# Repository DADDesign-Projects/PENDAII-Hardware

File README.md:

# PENDAII: Platform for Effects oN DAisy

Welcome to the **PENDAII** project! This repository contains the schematics and PCB layouts created with **KiCad 9.0** for a digital audio effects platform based on the **Daisy-Seed** board from **ElectroSmith**.

## Author

**DAD Design**

## Overview / Features

**PENDAII** is the second version of the PENDA platform. It introduces stereo processing and improved management of signal paths and power supplies.

**What’s New in PENDAII**:

- **Stereo processing**: a second audio channel has been added for a wider and more immersive sound experience.
- **Digital input volume control**: the input gain is now precisely adjustable via a digital potentiometer.
- **Digital Dry/Wet mix control**: the ratio between the processed (wet) and original (dry) signal is digitally managed.
- **100% analog Dry path**: although controlled digitally, the dry signal remains fully analog to preserve audio quality.

**General Features**:

- **Mono or Stereo Audio Input/Output**: flexible integration into various audio setups.
- **Two momentary footswitches**: for hands-free activation of effects.
- **2-inch SPI display**: clean and compact user interface (compatible with most ST7789 displays).
- **MIDI input**: allows control via external MIDI devices.
- **User controls**:
  - **4 encoders with push-button**: for parameter navigation and adjustment.
  - **3 analog potentiometers**: for direct control of parameters such as input level or Dry/Wet mix.

## Content

- The **Fab** directory contains all necessary files for fabrication.
- The **PENDAII-Hardware** directory contains the source files for the KiCad 9.0 project.

## Software

**PENDAII-Software** is a collection of audio effects built on an advanced software architecture, specifically designed for the PENDAII hardware platform.

[GitHub Repository](https://github.com/DADDesign-Projects/PENDAII-Software)

## Contributing

Contributions are welcome! If you'd like to suggest an improvement or fix an issue, feel free to open an *issue* or a *pull request*.

## License

This project is licensed under the **MIT License**.

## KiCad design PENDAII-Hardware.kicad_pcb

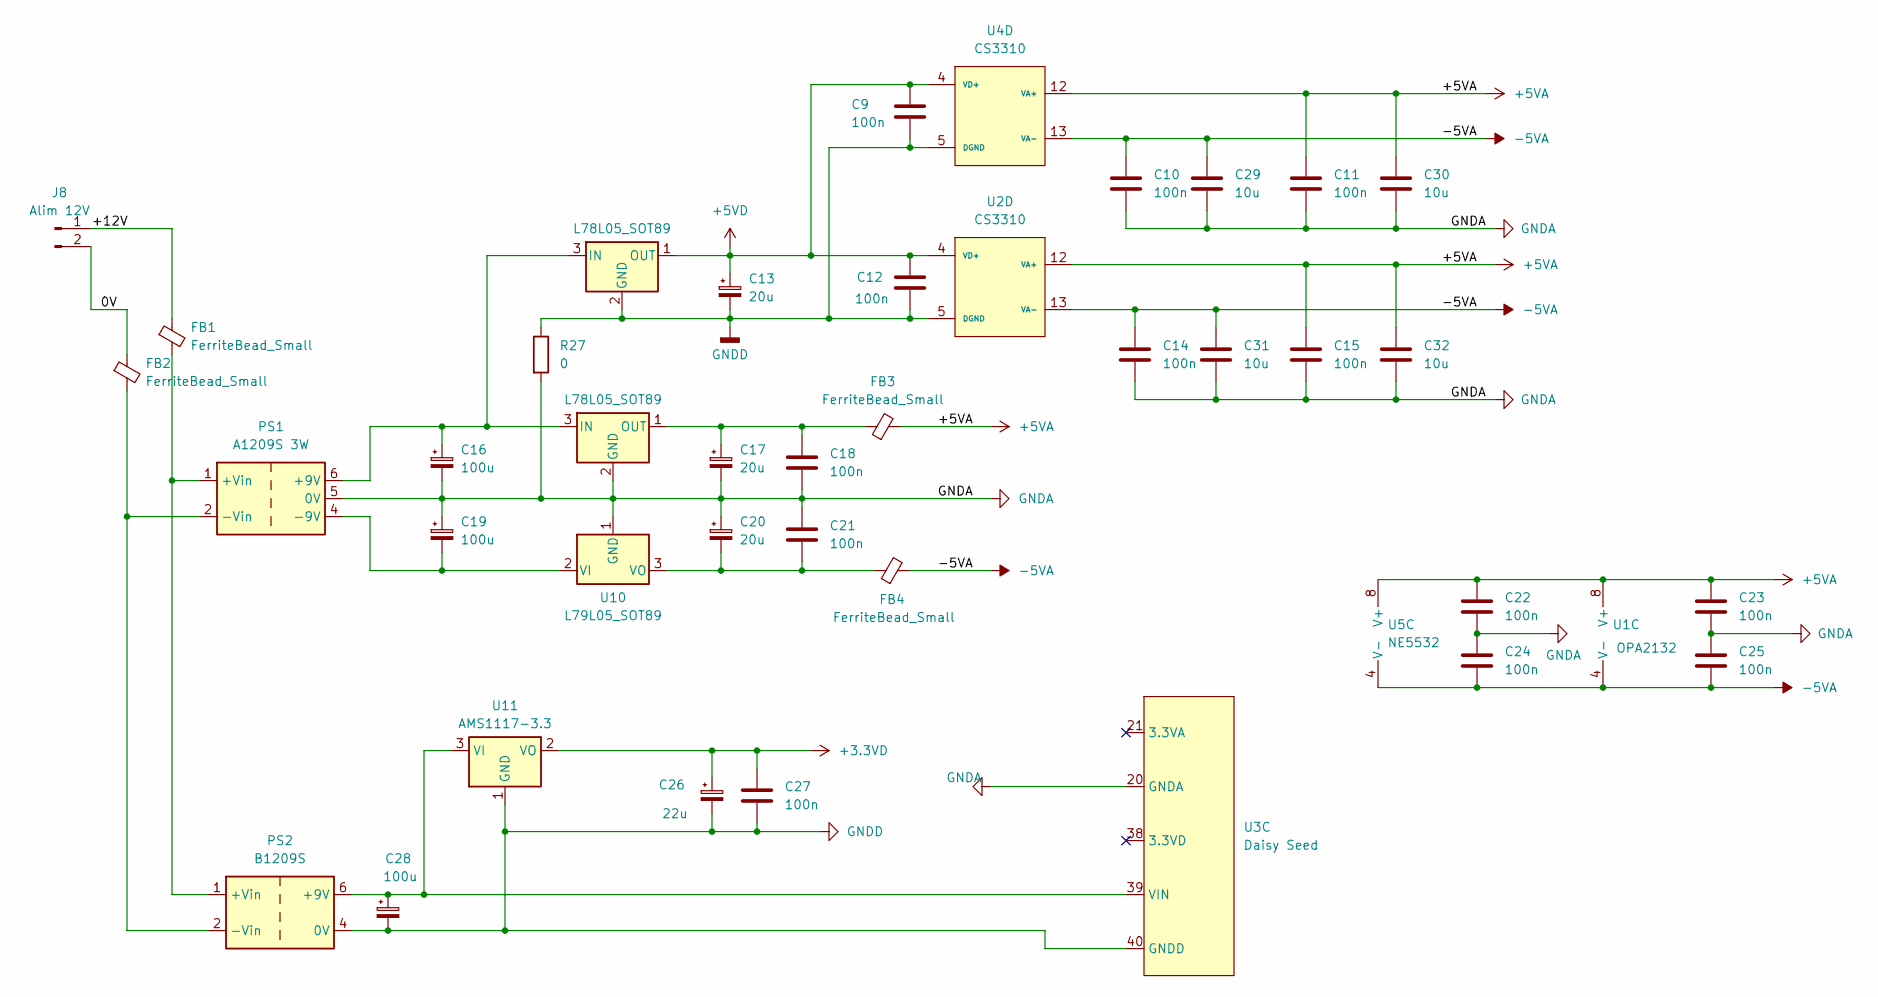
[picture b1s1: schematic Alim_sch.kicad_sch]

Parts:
C9, C10, C11, C12, C14, C15, C18, C21, C22, C23, C24, C25, C27: 100n; C_0805_2012Metric_Pad1.18x1.45mm_HandSolder
C13, C17, C20: 20u; CP_Elec_5x5.4
C16, C19, C28: 100u; CP_Elec_6.3x7.7
C26: 22u; CP_Elec_5x5.4
C29, C30, C31, C32: 10u; C_1206_3216Metric_Pad1.33x1.80mm_HandSolder
FB1, FB2: FerriteBead_Small; L_1206_3216Metric_Pad1.22x1.90mm_HandSolder
FB3, FB4: FerriteBead_Small; L_0805_2012Metric_Pad1.15x1.40mm_HandSolder
J8: Alim 12V; PinHeader_1x02_P2.54mm_Vertical
PS1: A1209S 3W; Converter_DCDC_TRACO_TBA2-xxxx_Dual_THT
PS2: B1209S; Converter_DCDC_TRACO_TBA2-xxxx_Single_THT
R27: 0; R_1206_3216Metric_Pad1.30x1.75mm_HandSolder
U1: OPA2132; SOP-8_3.76x4.96mm_P1.27mm
U2, U4: CS3310; SOIC-16W_7.5x10.3mm_P1.27mm
U3: Daisy Seed; DIP-40_W15.24mm_Socket_LongPads
U5: NE5532; SOP-8_3.76x4.96mm_P1.27mm
U8, U9: L78L05_SOT89; SOT-89-3
U10: L79L05_SOT89; SOT-89-3
U11: AMS1117-3.3; SOT-223-3_TabPin2

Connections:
+3.3VD: C26.1, C27.1, U11.2 (VO); also elsewhere on the board
+5VA: C11.1, C15.1, C22.1, C23.1, C30.1, C32.1, FB3.2, U1.8 (V+), U2.12 (VA+), U4.12 (VA+), U5.8 (V+)
+5VD: C9.1, C12.1, C13.1, U2.4 (VD+), U4.4 (VD+), U8.1 (OUT); also elsewhere on the board
-5VA: C10.1, C14.1, C24.2, C25.2, C29.1, C31.1, FB4.2, U1.4 (V-), U2.13 (VA-), U4.13 (VA-), U5.4 (V-)
/Alim/0V: FB2.1, J8.2
/Alim/+12V: FB1.1, J8.1
GNDA: C10.2, C11.2, C14.2, C15.2, C16.2, C17.2, C18.2, C19.1, C20.1, C21.1, C22.2, C23.2, C24.1, C25.1, C29.2, C30.2, C31.2, C32.2, PS1.5 (0V), R27.2, U3.20 (GNDA), U9.2 (GND), U10.1 (GND); also elsewhere on the board
GNDD: C9.2, C12.2, C13.2, C26.2, C27.2, C28.2, PS2.4 (0V), R27.1, U2.5 (DGND), U3.40 (GNDD), U4.5 (DGND), U8.2 (GND), U11.1 (GND); also elsewhere on the board
unnamed: C16.1, PS1.6 (+9V), U8.3 (IN), U9.3 (IN)
unnamed: FB1.2, PS1.1 (+Vin), PS2.1 (+Vin)
unnamed: C19.2, PS1.4 (-9V), U10.2 (VI)
unnamed: FB2.2, PS1.2 (-Vin), PS2.2 (-Vin)
unnamed: C28.1, PS2.6 (+9V), U3.39 (VIN), U11.3 (VI)
unnamed: C17.1, C18.1, FB3.1, U9.1 (OUT)
unnamed: C20.2, C21.2, FB4.1, U10.3 (VO)

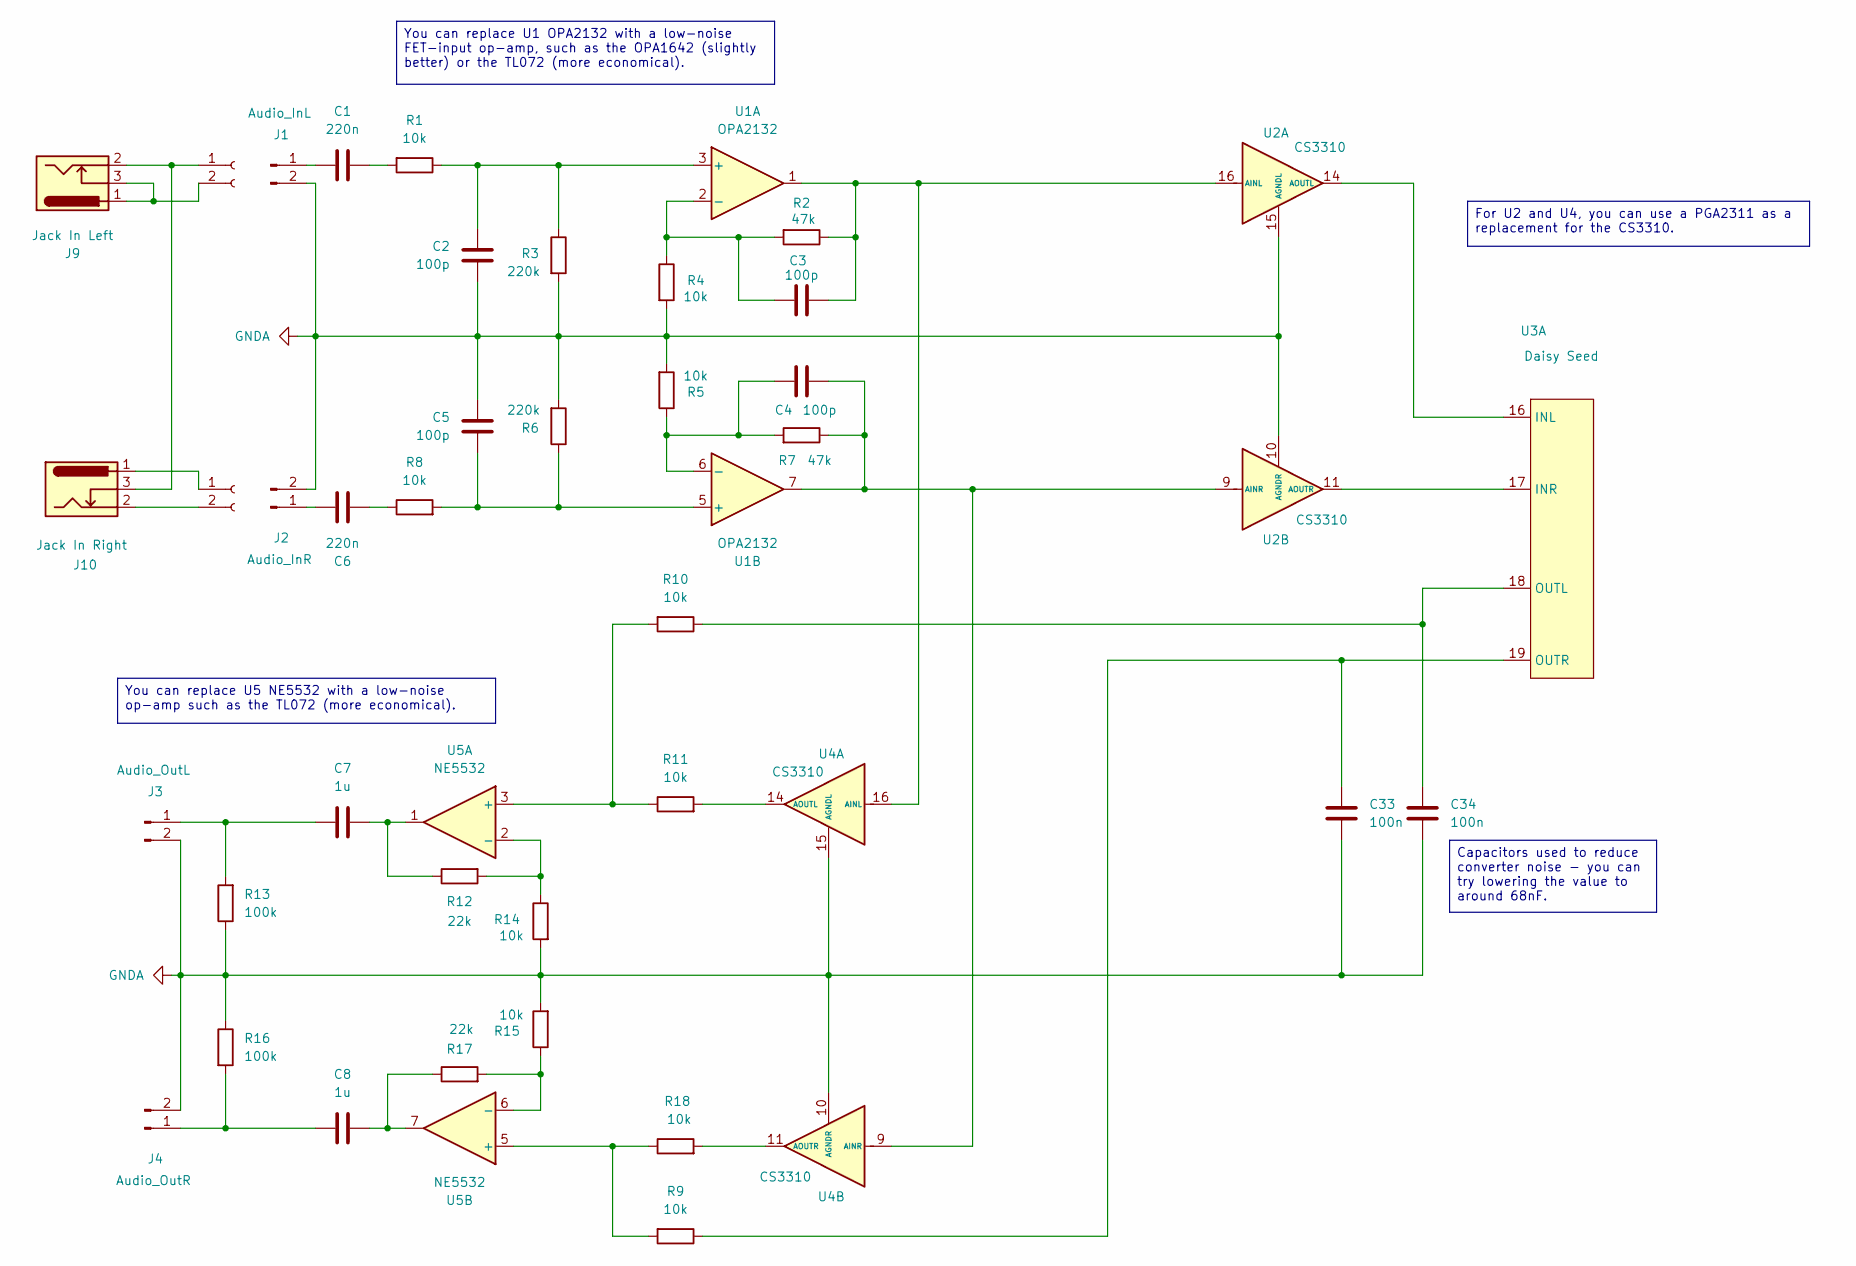
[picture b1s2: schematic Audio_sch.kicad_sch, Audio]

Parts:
C1, C6: 220n; C_1206_3216Metric_Pad1.33x1.80mm_HandSolder
C2, C3, C4, C5: 100p; C_1206_3216Metric_Pad1.33x1.80mm_HandSolder
C7, C8: 1u; C_1206_3216Metric_Pad1.33x1.80mm_HandSolder
C33, C34: 100n; C_0805_2012Metric_Pad1.18x1.45mm_HandSolder
J1: Audio_InL; PinHeader_1x02_P2.54mm_Vertical
J2: Audio_InR; PinHeader_1x02_P2.54mm_Vertical
J3: Audio_OutL; PinHeader_1x02_P2.54mm_Vertical
J4: Audio_OutR; PinHeader_1x02_P2.54mm_Vertical
J9: Jack In Left
J10: Jack In Right
J11: Conn_01x02_Socket
J12: (no value)
R1, R4, R5, R8, R9, R10, R11, R14, R15, R18: 10k; R_1206_3216Metric_Pad1.30x1.75mm_HandSolder
R2, R7: 47k; R_1206_3216Metric_Pad1.30x1.75mm_HandSolder
R3, R6: 220k; R_1206_3216Metric_Pad1.30x1.75mm_HandSolder
R12, R17: 22k; R_1206_3216Metric_Pad1.30x1.75mm_HandSolder
R13, R16: 100k; R_1206_3216Metric_Pad1.30x1.75mm_HandSolder
U1: OPA2132; SOP-8_3.76x4.96mm_P1.27mm
U2, U4: CS3310; SOIC-16W_7.5x10.3mm_P1.27mm
U3: Daisy Seed; DIP-40_W15.24mm_Socket_LongPads
U5: NE5532; SOP-8_3.76x4.96mm_P1.27mm

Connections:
GNDA: C2.1, C5.1, C33.2, C34.2, J1.2, J2.2, J3.2, J4.2, R3.2, R4.2, R5.2, R6.2, R13.1, R14.2, R15.2, R16.1, U2.10 (AGNDR), U2.15 (AGNDL), U4.10 (AGNDR), U4.15 (AGNDL); also elsewhere on the board
unnamed: C1.2, R1.2
unnamed: C6.2, R8.1
unnamed: C7.2, R12.1, U5.1
unnamed: C8.2, R17.1, U5.7
unnamed: C1.1, J1.1
unnamed: C6.1, J2.1
unnamed: C7.1, J3.1, R13.2
unnamed: C8.1, J4.1, R16.2
unnamed: J10.1, J12.1
unnamed: J10.2, J12.2
unnamed: J9.2, J10.3, J11.1
unnamed: J9.1, J9.3, J11.2
unnamed: C2.2, R1.1, R3.1, U1.3 (+)
unnamed: C3.1, R2.2, R4.1, U1.2 (-)
unnamed: C5.2, R6.1, R8.2, U1.5 (+)
unnamed: C4.1, R5.1, R7.2, U1.6 (-)
unnamed: C3.2, R2.1, U1.1, U2.16 (AINL), U4.16 (AINL)
unnamed: U2.14 (AOUTL), U3.16 (INL)
unnamed: C4.2, R7.1, U1.7, U2.9 (AINR), U4.9 (AINR)
unnamed: U2.11 (AOUTR), U3.17 (INR)
unnamed: C34.1, R10.1, U3.18 (OUTL)
unnamed: C33.1, R9.1, U3.19 (OUTR)
unnamed: R11.2, U4.14 (AOUTL)
unnamed: R18.2, U4.11 (AOUTR)
unnamed: R10.2, R11.1, U5.3 (+)
unnamed: R12.2, R14.1, U5.2 (-)
unnamed: R9.2, R18.1, U5.5 (+)
unnamed: R15.1, R17.2, U5.6 (-)

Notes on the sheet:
You can replace U5 NE5532 with a low-noise op-amp such as the TL072 (more economical).
You can replace U1 OPA2132 with a low-noise FET-input op-amp, such as the OPA1642 (slightly better) or the TL072 (more economical).
For U2 and U4, you can use a PGA2311 as a replacement for the CS3310.
Capacitors used to reduce converter noise - you can try lowering the value to around 68nF.

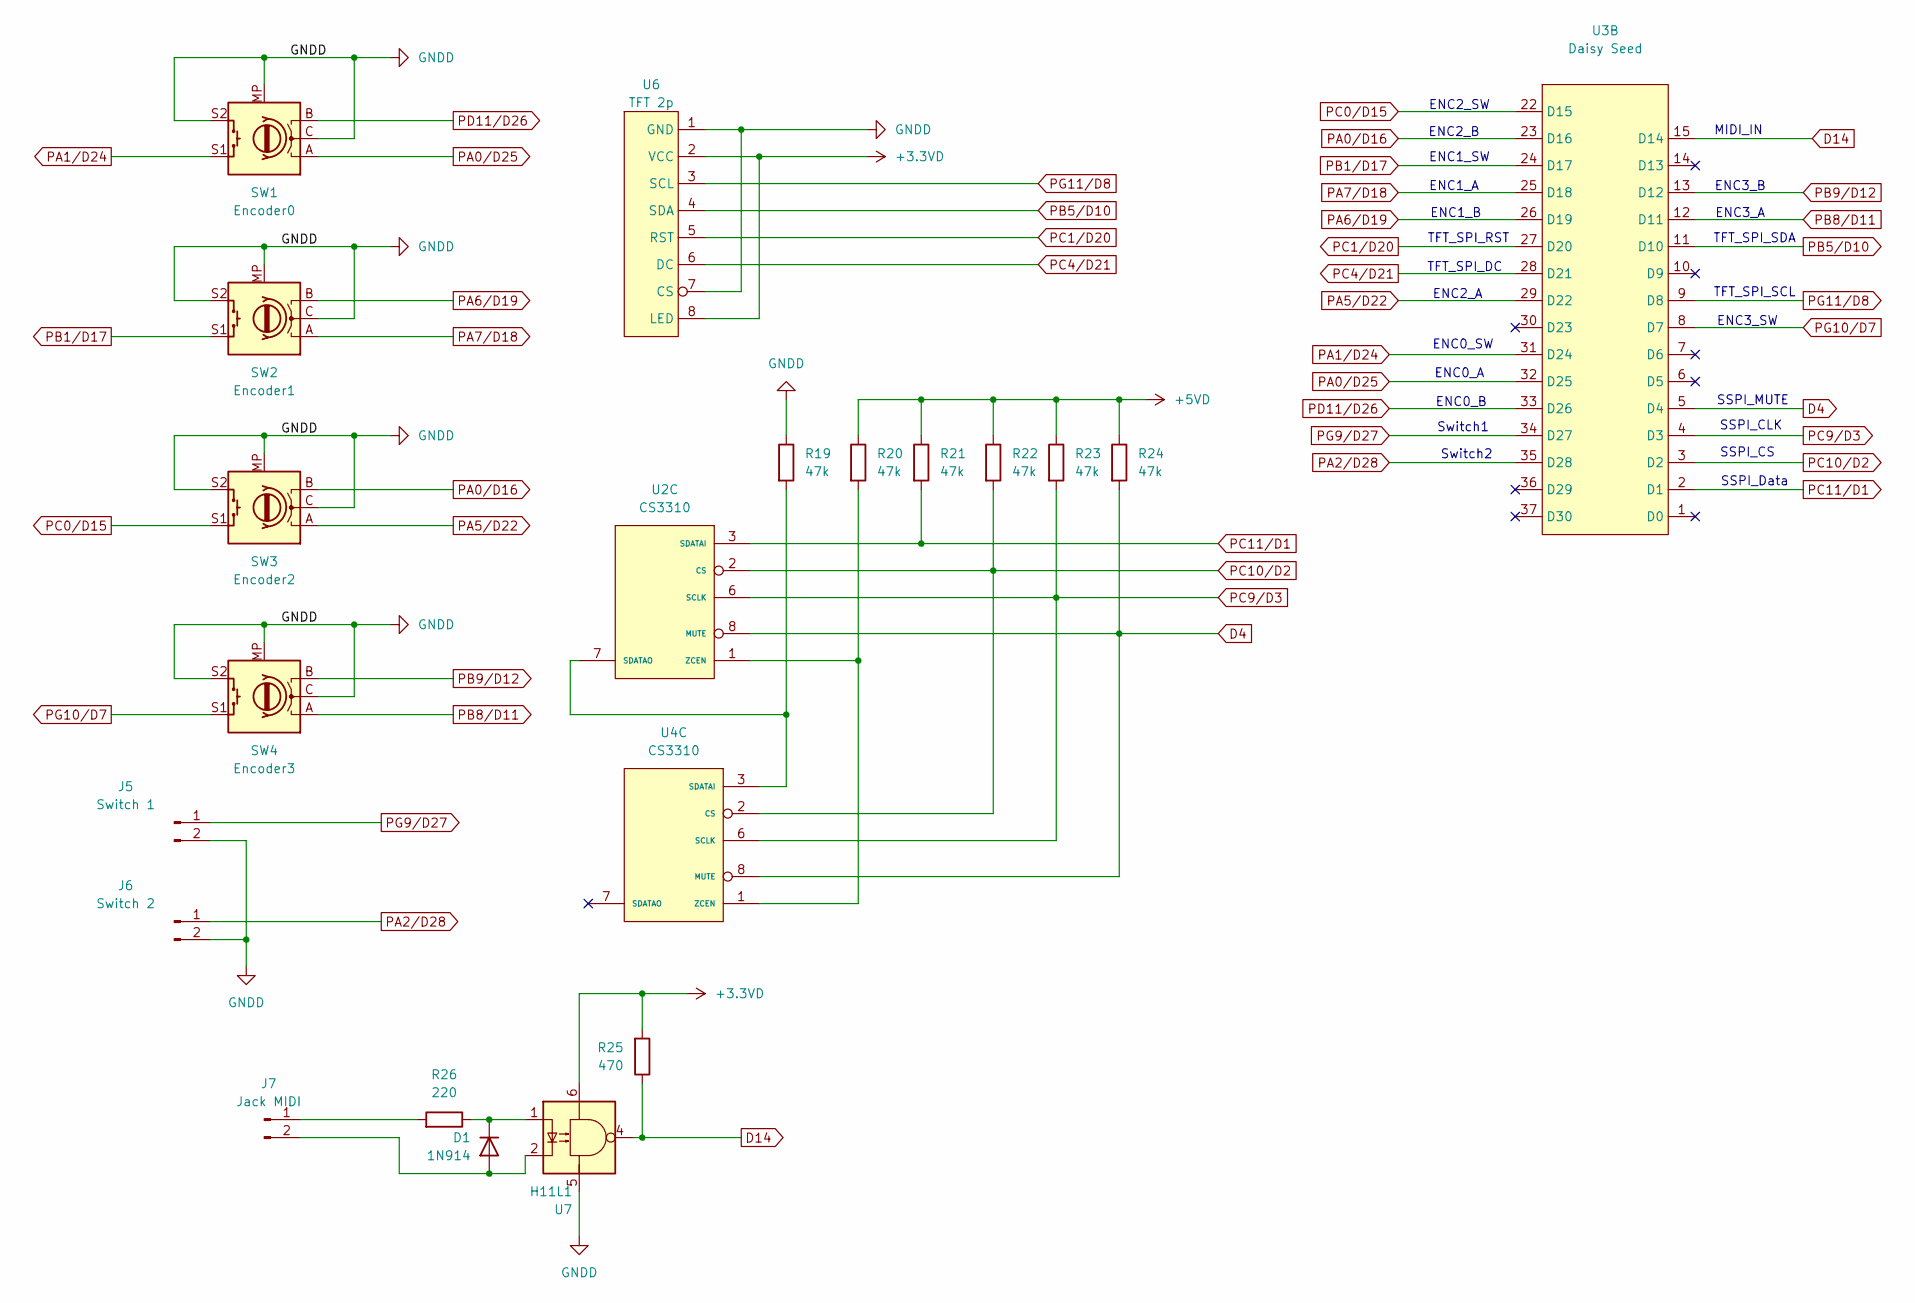
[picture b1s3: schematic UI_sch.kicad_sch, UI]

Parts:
D1: 1N914; D_DO-35_SOD27_P7.62mm_Horizontal
J5: Switch 1; PinHeader_1x02_P2.54mm_Vertical
J6: Switch 2; PinHeader_1x02_P2.54mm_Vertical
J7: Jack MIDI; PinHeader_1x02_P2.54mm_Vertical
R19, R20, R21, R22, R23, R24: 47k; R_1206_3216Metric_Pad1.30x1.75mm_HandSolder
R25: 470; R_Axial_DIN0204_L3.6mm_D1.6mm_P7.62mm_Horizontal
R26: 220; R_Axial_DIN0204_L3.6mm_D1.6mm_P7.62mm_Horizontal
SW1: Encoder0; RotaryEncoder_Alps_EC11E-Switch_Vertical_H20mm
SW2: Encoder1; RotaryEncoder_Alps_EC11E-Switch_Vertical_H20mm
SW3: Encoder2; RotaryEncoder_Alps_EC11E-Switch_Vertical_H20mm
SW4: Encoder3; RotaryEncoder_Alps_EC11E-Switch_Vertical_H20mm
U2, U4: CS3310; SOIC-16W_7.5x10.3mm_P1.27mm
U3: Daisy Seed; DIP-40_W15.24mm_Socket_LongPads
U6: TFT 2p; PinSocket_1x08_P2.54mm_Vertical
U7: H11L1; DIP-6_W7.62mm

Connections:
+3.3VD: R25.2, U6.2 (VCC), U6.8 (LED), U7.6; also elsewhere on the board
+5VD: R20.1, R21.1, R22.1, R23.1, R24.1; also elsewhere on the board
D4: R24.2, U2.8 (MUTE), U3.5 (D4), U4.8 (MUTE)
D14: R25.1, U3.15 (D14), U7.4
GNDD: J5.2, J6.2, R19.1, SW1.C, SW1.MP, SW1.S2, SW2.C, SW2.MP, SW2.S2, SW3.C, SW3.MP, SW3.S2, SW4.C, SW4.MP, SW4.S2, U6.1 (GND), U6.7 (CS), U7.5; also elsewhere on the board
unnamed: D1.2 (A), J7.2, U7.2
unnamed: D1.1 (K), R26.1, U7.1
unnamed: J7.1, R26.2
unnamed: R19.2, U2.7 (SDATAO), U4.3 (SDATAI)
unnamed: R20.2, U2.1 (ZCEN), U4.1 (ZCEN)
PA0/D16: SW3.B, U3.23 (D16)
PA0/D25: SW1.A, U3.32 (D25)
PA1/D24: SW1.S1, U3.31 (D24)
PA2/D28: J6.1, U3.35 (D28)
PA5/D22: SW3.A, U3.29 (D22)
PA6/D19: SW2.B, U3.26 (D19)
PA7/D18: SW2.A, U3.25 (D18)
PB1/D17: SW2.S1, U3.24 (D17)
PB5/D10: U3.11 (D10), U6.4 (SDA)
PB8/D11: SW4.A, U3.12 (D11)
PB9/D12: SW4.B, U3.13 (D12)
PC0/D15: SW3.S1, U3.22 (D15)
PC1/D20: U3.27 (D20), U6.5 (RST)
PC4/D21: U3.28 (D21), U6.6 (DC)
PC9/D3: R23.2, U2.6 (SCLK), U3.4 (D3), U4.6 (SCLK)
PC10/D2: R22.2, U2.2 (CS), U3.3 (D2), U4.2 (CS)
PC11/D1: R21.2, U2.3 (SDATAI), U3.2 (D1)
PD11/D26: SW1.B, U3.33 (D26)
PG9/D27: J5.1, U3.34 (D27)
PG10/D7: SW4.S1, U3.8 (D7)
PG11/D8: U3.9 (D8), U6.3 (SCL)

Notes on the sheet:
ENC1_B
Switch1
ENC1_A
TFT_SPI_DC
Switch2
TFT_SPI_SCL
ENC2_SW
ENC2_A
ENC0_SW
ENC2_B
ENC3_SW
ENC3_A
ENC0_B
ENC3_B
SSPI_MUTE
TFT_SPI_RST
SSPI_CLK
SSPI_Data
ENC1_SW
TFT_SPI_SDA
SSPI_CS
MIDI_IN
ENC0_A

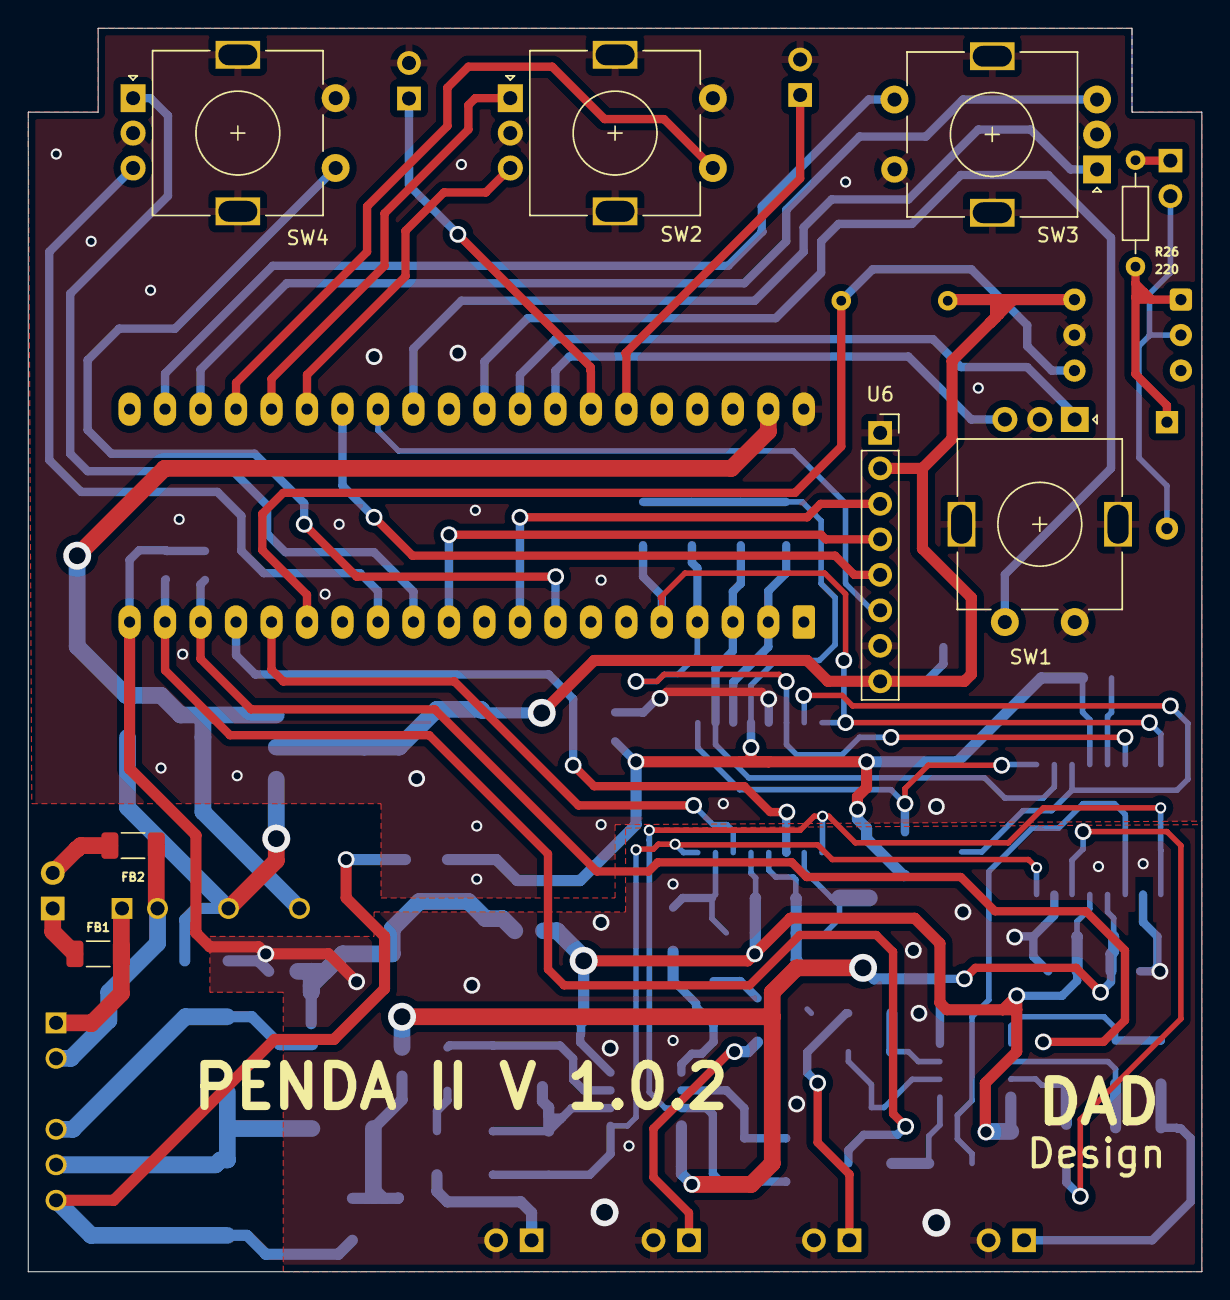
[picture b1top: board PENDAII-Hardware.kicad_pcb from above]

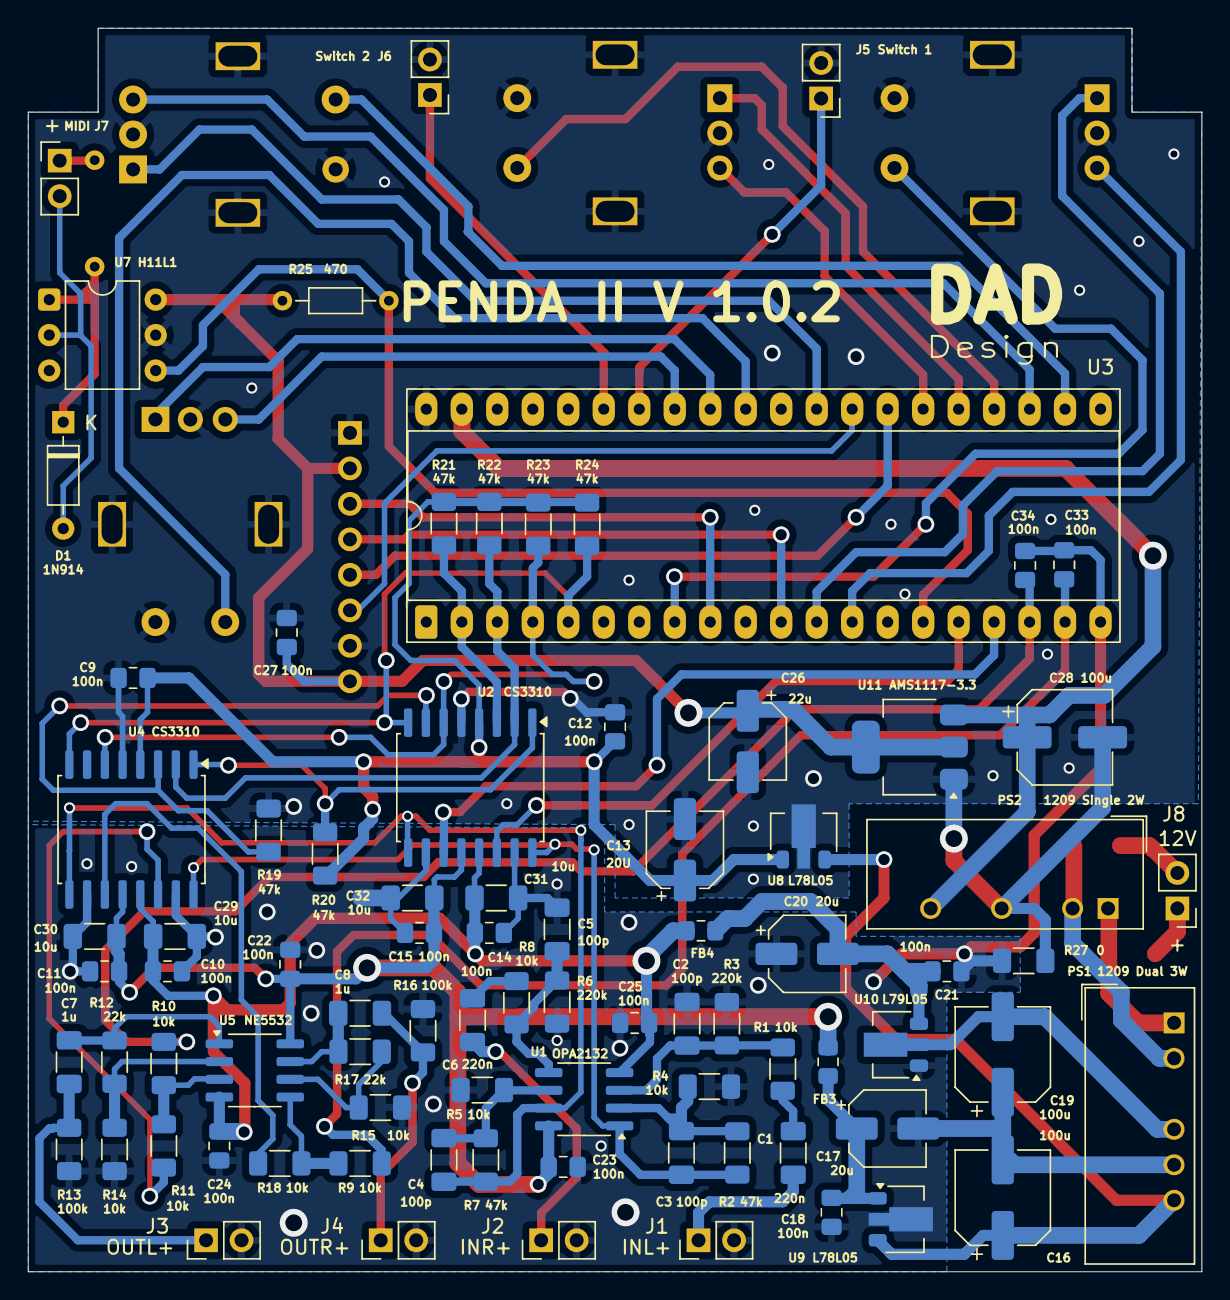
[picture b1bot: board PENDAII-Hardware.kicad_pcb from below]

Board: 2 copper layers, 84.0 x 89.0 mm, 91 parts (83 on the bottom side), 67 nets.

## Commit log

2025-05-23 New Routing
